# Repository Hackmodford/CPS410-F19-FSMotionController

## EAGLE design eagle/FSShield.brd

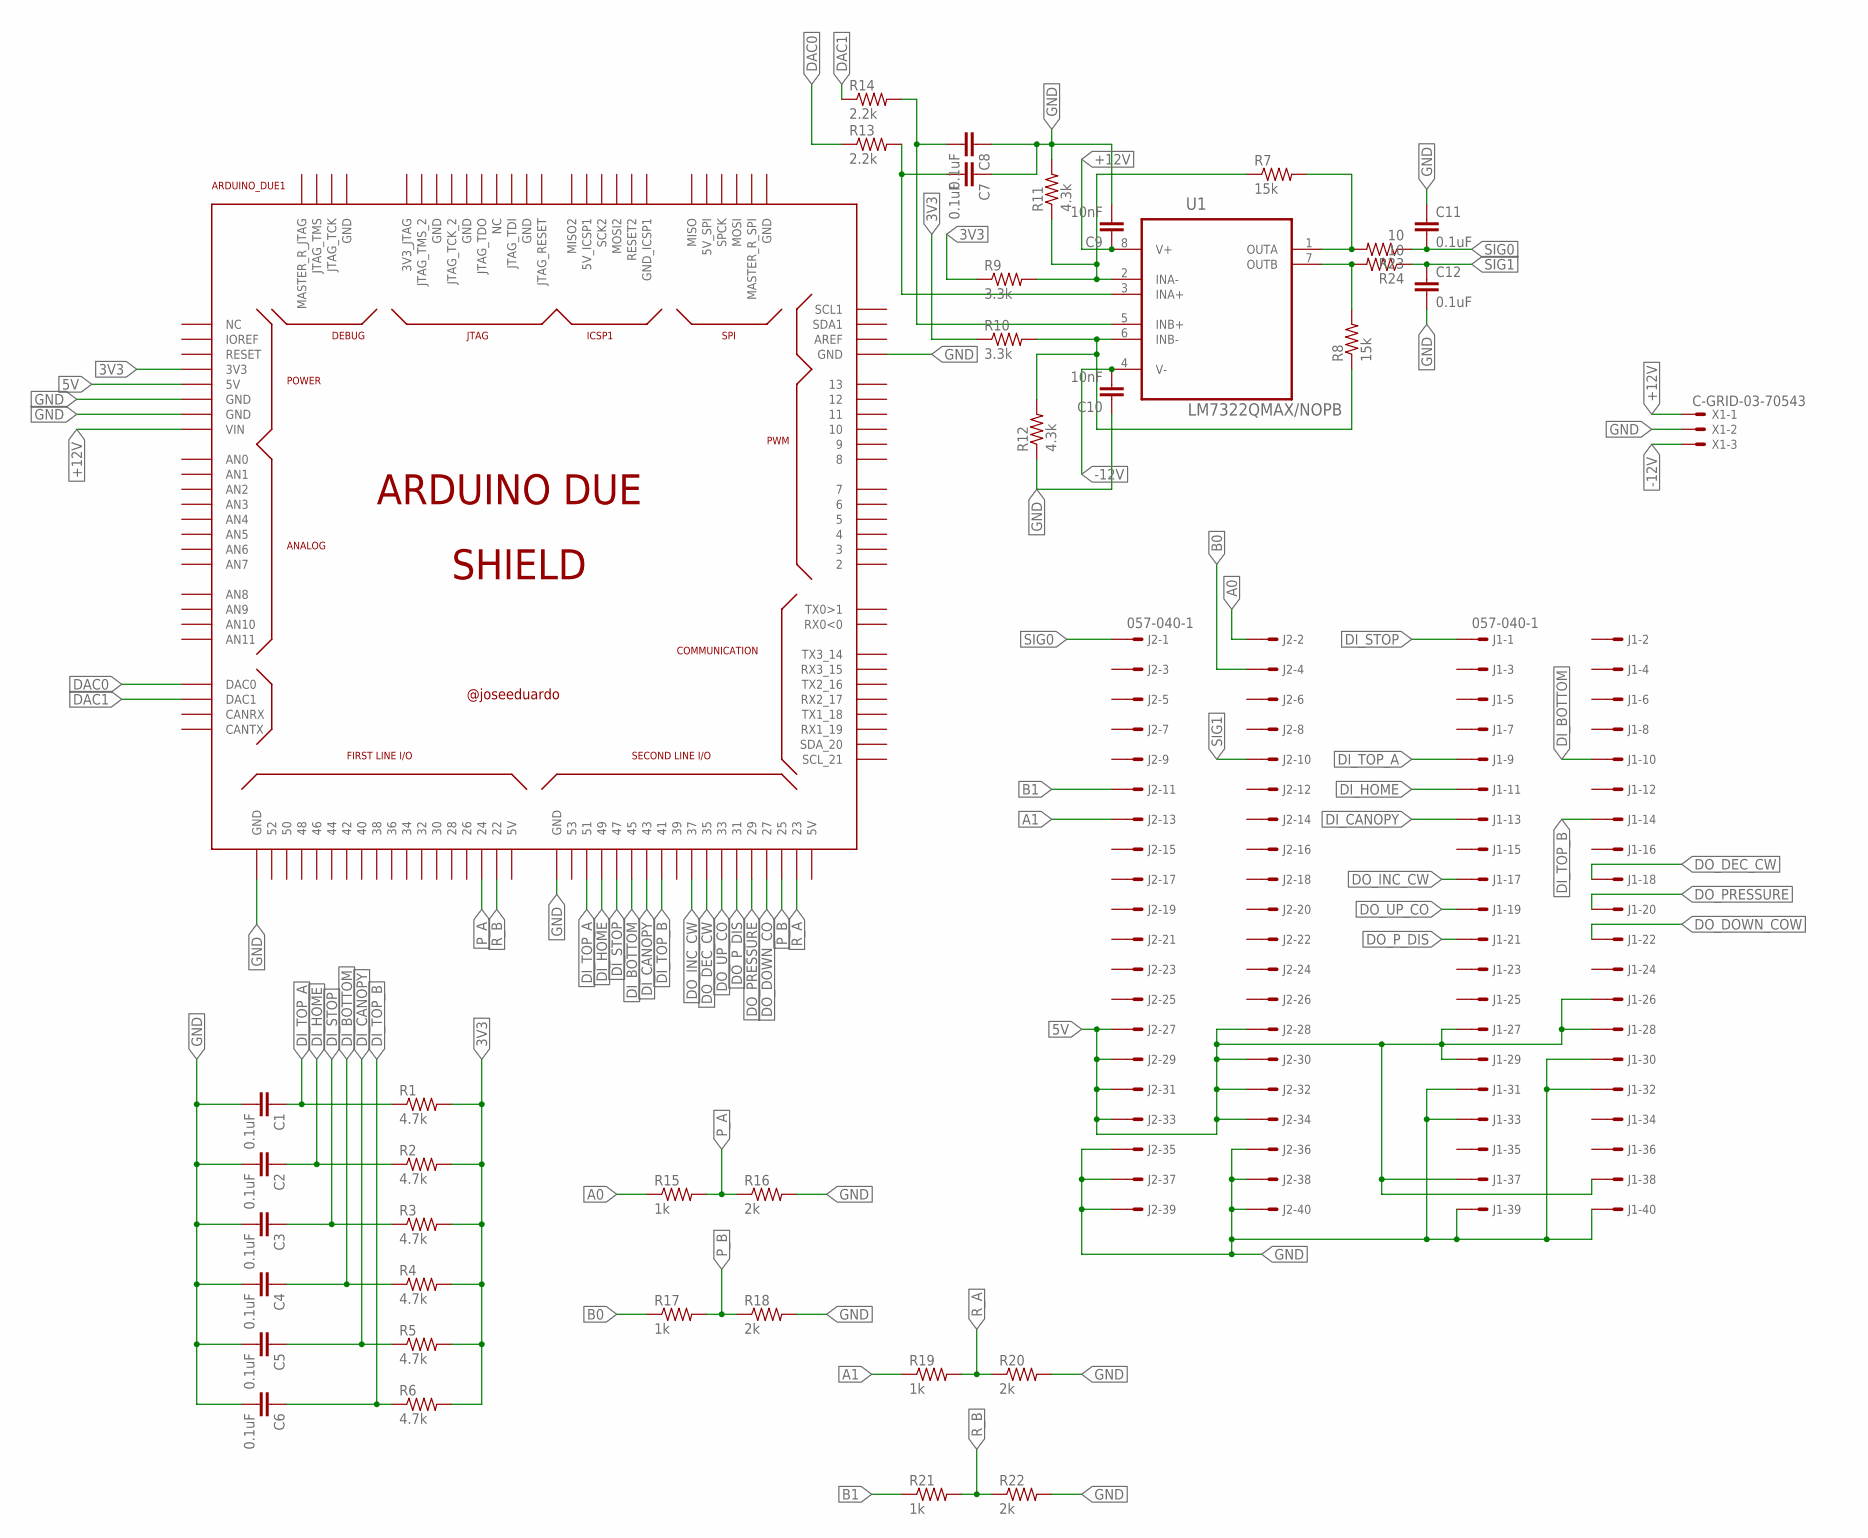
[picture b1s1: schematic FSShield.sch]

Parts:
ARDUINO_DUE1: ARDUINO_DUE_SHIELD
C1, C2, C3, C4, C5, C6, C7, C8, C11, C12: 0.1uF; 0603
C9, C10: 10nF; 0603
J1, J2: 057-040-1
R1, R2, R3, R4, R5, R6: 4.7k; M0805
R7, R8: 15k; M0805
R9, R10: 3.3k; M0805
R11, R12: 4.3k; M0805
R13, R14: 2.2k; M0805
R15, R17, R19, R21: 1k; M0805
R16, R18, R20, R22: 2k; M0805
R23, R24: 10; M0805
U1: LM7322QMAX/NOPB; SOIC127P600X175-8N
X1: C-GRID-03-70543; 70543-03

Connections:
3V3: ARDUINO_DUE1.3V3, R1.2, R2.2, R3.2, R4.2, R5.2, R6.2, R9.1, R10.1
5V: ARDUINO_DUE1.5V0 (5V), J1.26, J1.27, J1.28, J1.29, J1.37, J1.38, J2.27, J2.28, J2.29, J2.30, J2.31, J2.32, J2.33, J2.34
+12V: ARDUINO_DUE1.VIN, C9.1, U1.8 (V+), X1.1
-12V: C10.2, U1.4 (V-), X1.3
A0: J2.2, R15.1
A1: J2.13, R19.1
B0: J2.4, R17.1
B1: J2.11, R21.1
DAC0: ARDUINO_DUE1.DAC0, R13.1
DAC1: ARDUINO_DUE1.DAC1, R14.1
DI_BOTTOM: ARDUINO_DUE1.45, C4.1, J1.10, R4.1
DI_CANOPY: ARDUINO_DUE1.43, C5.1, J1.13, R5.1
DI_HOME: ARDUINO_DUE1.49, C2.1, J1.11, R2.1
DI_STOP: ARDUINO_DUE1.47, C3.1, J1.1, R3.1
DI_TOP_A: ARDUINO_DUE1.51, C1.1, J1.9, R1.1
DI_TOP_B: ARDUINO_DUE1.41, C6.1, J1.14, R6.1
DO_DEC_CW: ARDUINO_DUE1.35, J1.18
DO_DOWN_CO: ARDUINO_DUE1.27
DO_DOWN_COW: J1.22
DO_INC_CW: ARDUINO_DUE1.37, J1.17
DO_PRESSURE: ARDUINO_DUE1.29, J1.20
DO_P_DIS: ARDUINO_DUE1.31, J1.21
DO_UP_CO: ARDUINO_DUE1.33, J1.19
GND: ARDUINO_DUE1.GND, ARDUINO_DUE1.GND_1 (GND), ARDUINO_DUE1.GND_2 (GND), ARDUINO_DUE1.GND_3 (GND), ARDUINO_DUE1.GND_4 (GND), C1.2, C2.2, C3.2, C4.2, C5.2, C6.2, C7.1, C8.1, C9.2, C10.1, C11.1, C12.2, J1.30, J1.31, J1.32, J1.33, J1.39, J1.40, J2.35, J2.36, J2.37, J2.38, J2.39, J2.40, R11.2, R12.1, R16.2, R18.2, R20.2, R22.2, X1.2
unnamed: R7.1, R9.2, R11.1, U1.2 (INA-)
unnamed: R8.1, R10.2, R12.2, U1.6 (INB-)
unnamed: C7.2, R13.2, U1.3 (INA+)
unnamed: C8.2, R14.2, U1.5 (INB+)
unnamed: C12.1, R24.1
unnamed: C11.2, R23.1
P_A: ARDUINO_DUE1.24, R15.2, R16.1
P_B: ARDUINO_DUE1.25, R17.2, R18.1
R_A: ARDUINO_DUE1.23, R19.2, R20.1
R_B: ARDUINO_DUE1.22, R21.2, R22.1
SIG0: J2.1, R7.2, R23.2, U1.1 (OUTA)
SIG1: J2.10, R8.2, R24.2, U1.7 (OUTB)

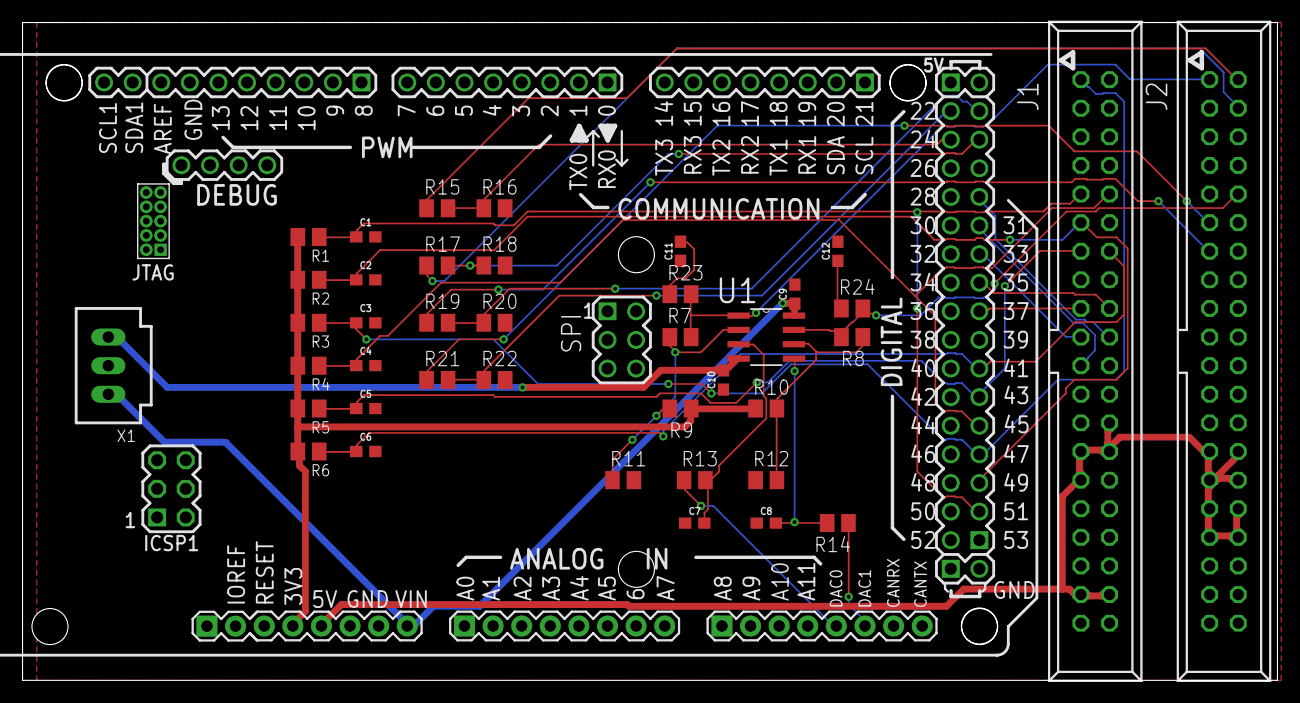
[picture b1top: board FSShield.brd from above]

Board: 2 copper layers, 111.4 x 58.4 mm, 41 parts (0 on the bottom side), 34 nets.

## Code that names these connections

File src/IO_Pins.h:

#define DI_TOP_A 51
#define DI_HOME 49
#define DI_STOP 47
#define DI_BOTTOM 45
#define DI_CANOPY 43
#define DI_TOP_B 41

#define DO_INC_CW 37
#define DO_DEC_CW 35
#define DO_UP_CO 33
#define DO_P_DIS 31
#define DO_PRESSURE 29
#define DO_DOWN_CO 27

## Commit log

2019-10-01 Added code to detect udp commands
2019-10-01 Sends data to monitor application via UDP.
2019-10-01 Added preliminary state handling. Added sending data back to console using UDP. Handles more commands from UDP.
2019-10-06 Added communication over ethernet.
2019-10-08 Serial is only used for debugging. Fixed crash.
2019-10-08 Removed "#if Debug"
2019-10-08 Added ability to read configuration file.
2019-10-09 Minor changes
2019-10-10 Added DAC controller
2019-10-11 trying to get branches up to date
2019-10-11 constrained fine gain input
2019-10-11 removed .DS_Store file
2019-10-15 Added commands for changing DAC settings
2019-10-15 Added preliminary support for stop switches.
2019-10-22 Arduino debugging working. Fixed SPI communication
2019-10-22 Added preliminary manual movement support.
2019-10-24 Code works with AD5764 Eval Board!
2019-10-25 Added ability to move manually with btns.
2019-10-28 Added physical manual controls.
2019-10-28 Main loop sets DAC to zero when not in use.
2019-10-31 Refactored code
2019-11-10 Tweaks for GUI support
2019-11-10 Added support for set switches.
2019-11-12 updated pin numbers
2019-11-14 Fix overflow error when mapping setpoints.
2019-11-14 Accepts BigEndian setpoints from SimTools
2019-11-15 ADDED IO REPORTING. Fixed pins.
2019-11-15 Fixed IO
2019-11-19 Fixed IO reporting.
2019-11-21 pin adjustments
2019-11-22 Fix incorrect pins
2019-11-22 Updated encoders values
2019-11-22 Added delay to raising command when reaching setpoint.
2019-12-04 Fixed encoder values. Using degrees for roll state
2019-12-04 Now using Arduino DAC with OpAmp
2019-12-06 Fix max DAC value.
2019-12-06 added comments, changed variable name
2019-12-12 Added EAGLE schematic and board.
2019-12-13 removed DAC code. Updated eagle files.

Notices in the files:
parts and their libraries:
SparkFun-Capacitors: Licensing: Creative Commons ShareAlike 4.0 International - https://creativecommons.org/licenses/by-sa/4.0
